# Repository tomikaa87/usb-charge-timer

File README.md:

# usb-charge-timer
Simple timer to turn off a USB charger automatically.

Based on the small PIC12F683 microcontroller.
The turn off time can be set with only one button.
A single LED indicator shows the state and the set time.

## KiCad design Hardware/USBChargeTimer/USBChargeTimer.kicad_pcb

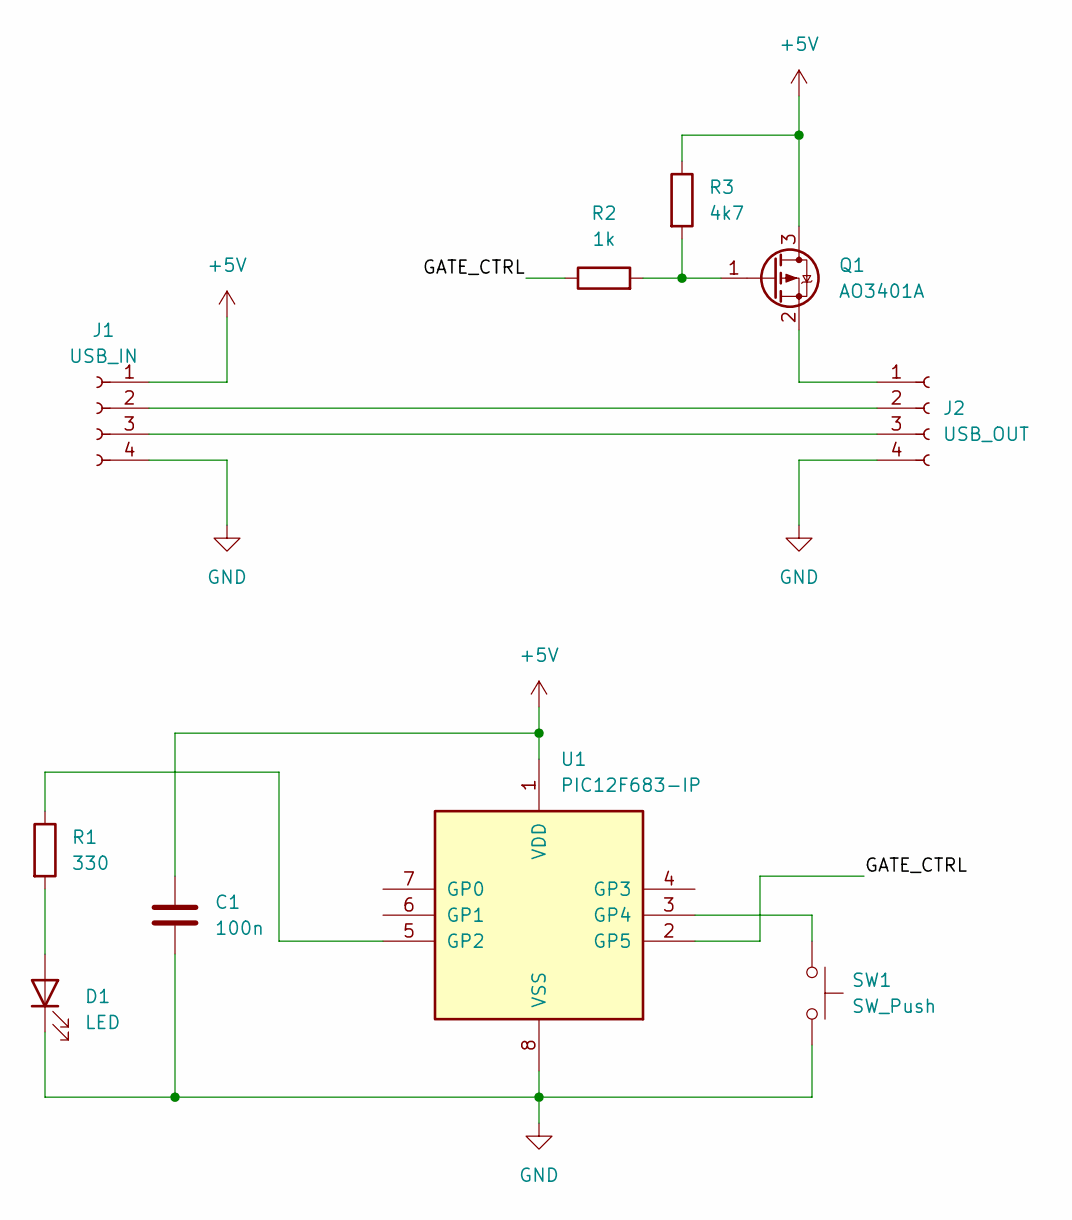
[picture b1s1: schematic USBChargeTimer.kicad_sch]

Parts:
C1: 100n; C_Disc_D3.0mm_W1.6mm_P2.50mm
D1: LED; LED_D3.0mm
J1: USB_IN; PinHeader_1x04_P2.54mm_Vertical
J2: USB_OUT; PinHeader_1x04_P2.54mm_Vertical
Q1: AO3401A; SOT-23
R1: 330; R_Axial_DIN0204_L3.6mm_D1.6mm_P2.54mm_Vertical
R2: 1k; R_Axial_DIN0204_L3.6mm_D1.6mm_P2.54mm_Vertical
R3: 4k7; R_Axial_DIN0204_L3.6mm_D1.6mm_P2.54mm_Vertical
SW1: SW_Push; SW_PUSH_6mm
U1: PIC12F683-IP; DIP-8_W7.62mm

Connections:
+5V: C1.1, J1.1, Q1.3 (D), R3.1, U1.1 (VDD)
/GATE_CTRL: R2.1, U1.2 (GP5)
GND: C1.2, D1.1 (K), J1.4, J2.4, SW1.2, U1.8 (VSS)
unnamed: D1.2 (A), R1.2
unnamed: J1.2, J2.2
unnamed: J1.3, J2.3
unnamed: J2.1, Q1.2 (S)
unnamed: Q1.1 (G), R2.2, R3.2
unnamed: R1.1, U1.5 (GP2)
unnamed: SW1.1, U1.3 (GP4)

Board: 2 copper layers, 10 parts (1 on the bottom side), 10 nets, no tracks yet.

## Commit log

2022-12-30 Initial commit of the firmware
2023-01-01 Adjust output polarity for high-side drive
2023-01-01 Disable unnecessary/unused CPU features
2023-01-01 PCB: add initial version of the schematics
